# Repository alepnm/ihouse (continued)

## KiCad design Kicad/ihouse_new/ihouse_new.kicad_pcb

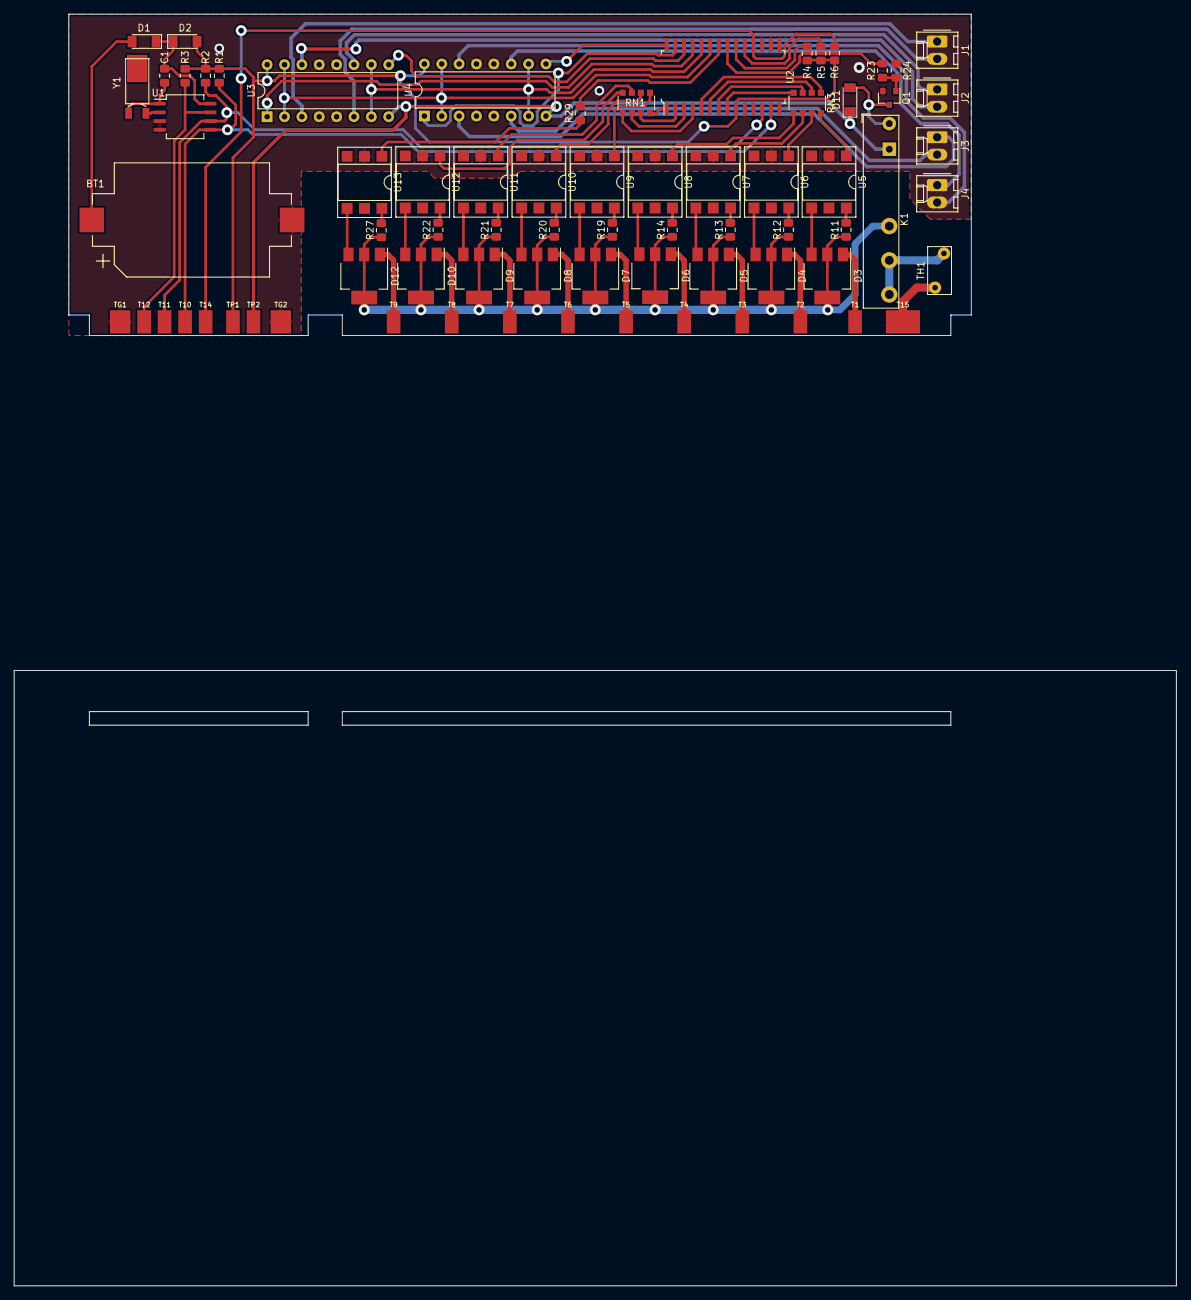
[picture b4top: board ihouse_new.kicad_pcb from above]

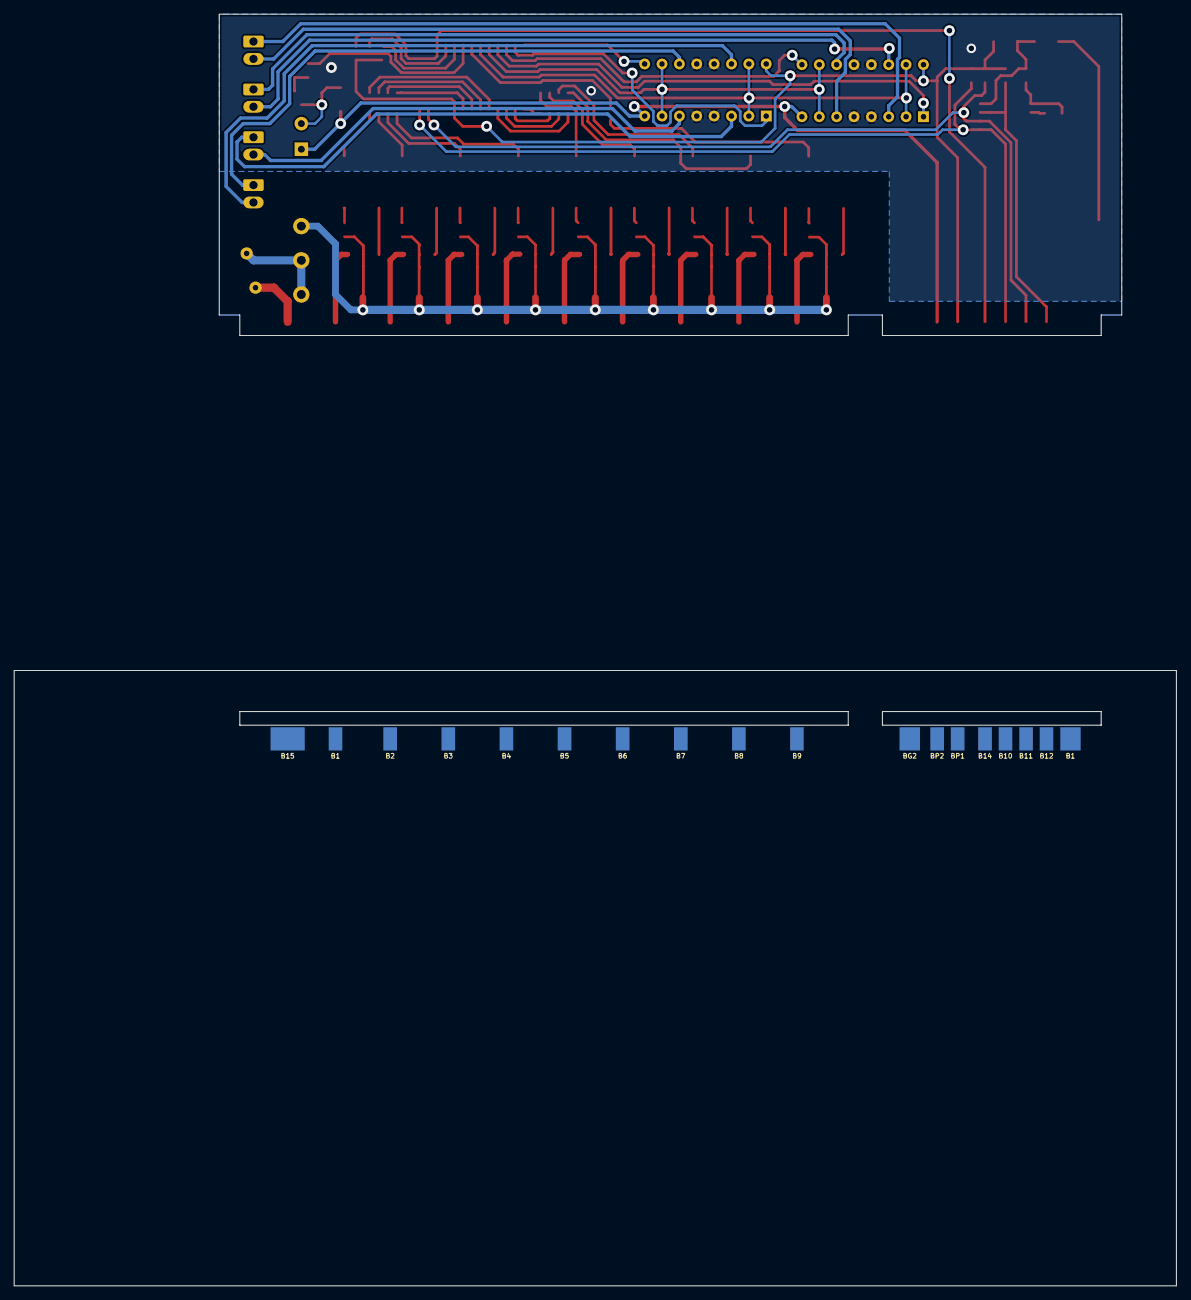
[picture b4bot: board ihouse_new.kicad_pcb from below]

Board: 2 copper layers, 132.0 x 47.0 mm, 91 parts (18 on the bottom side), 78 nets.

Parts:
B1, B1#2, B2, B3, B4, B5, B6, B7, B8, B9, B10, B11, B12, B14, B15: Conn_01x01; Sold_Pad
BG2: Conn_01x01; Sold_Pad
BP1, BP2: Conn_01x01; Sold_Pad
BT1: CR2032; BatteryHolder_Keystone_1060_1x2032
C1: 22p; C_0805_2012Metric_Pad1.15x1.40mm_HandSolder
D1: BAS85; D_MiniMELF
D2, D11: BAS32; D_MiniMELF
D3, D4, D5, D6, D7, D8, D9, D10, D12: Z0103MN; SOT-223
J1, J2, J3, J4: Valve 1; Molex_KK-254_AE-6410-02A_1x02_P2.54mm_Vertical
K1: FINDER-32.21-x000; Relay_SPDT_Finder_34.51_Vertical
Q1: BC817; SOT-23
R1, R2, R3, R4, R5, R6: 4.7k; R_0805_2012Metric_Pad1.15x1.40mm_HandSolder
R11, R12, R13, R14, R19, R20, R21, R22, R27, R29: 470; R_0805_2012Metric_Pad1.15x1.40mm_HandSolder
R23: 10k; R_0805_2012Metric_Pad1.15x1.40mm_HandSolder
R24: 1k; R_0805_2012Metric_Pad1.15x1.40mm_HandSolder
RN1, RN3: R_Pack04; R_Array_Convex_4x1206
T1, T2, T3, T4, T5, T6, T7, T8, T9, T10, T11, T12, T14, T15: Conn_01x01; Sold_Pad
TG1, TG2: Conn_01x01; Sold_Pad
TH1: Thermistor_PTC; RV_Disc_D7mm_W3.5mm_P5mm
TP1, TP2: Conn_01x01; Sold_Pad
U1: PCF8583T; SO-8_5.3x6.2mm_P1.27mm
U2: MCP23017-E_SO; SOIC-28_W7.5mm
U3, U4: L293D; DIP-16_W7.62mm
U5, U6, U7, U8, U9, U10, U11, U12, U13: MOC3063M; DIP-6_W7.62mm_SMDSocket_SmallPads
Y1: 32768; Crystal_SMD_FrontierElectronics_FM206

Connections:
+5V: BP1.1, D2.2, R1.1, R2.1, R3.1, R4.1, R5.1, R6.1, TP1.1, U2.9, U3.16, U4.16
+15V: BP2.1, D11.1, K1.A1, TP2.1, U3.8, U4.8
/ACL: D3.2, D3.4, D4.2, D4.4, D5.2, D5.4, D6.2, D6.4, D7.2, D7.4, D8.2, D8.4, D9.2, D9.4, D10.2, D10.4, D12.2, D12.4, K1.12, R11.1, R12.1, R13.1, R14.1, R19.1, R20.1, R21.1, R22.1, R27.1
/ACON: R23.2, U2.21
/M1ENA: U2.25, U3.1
/M2ENA: U2.26, U3.9
/M3ENA: U2.27, U4.1
/M4ENA: U2.28, U4.9
/MA: U2.23, U3.2, U3.15, U4.2, U4.15
/MB: U2.24, U3.7, U3.10, U4.7, U4.10
/OC1: RN3.8, U5.1
/OC2: RN3.7, U6.1
/OC3: RN3.6, U7.1
/OC4: RN3.5, U8.1
/OC5: RN1.5, U9.1
/OC6: RN1.6, U10.1
/OC7: RN1.7, U11.1
/OC8: RN1.8, U12.1
/OC9: R29.1, U13.1
/SCL: B11.1, R2.2, T11.1, U1.6, U2.12
/SDA: B10.1, R1.2, T10.1, U1.5, U2.13
/~INT: B12.1, R3.2, T12.1, U1.7
/~INTA: R4.2, U2.20
/~INTB: R5.2, U2.19
/~RST: B14.1, R6.2, T14.1, U2.18
GND: B1.1, BG2.1, BT1.2, Q1.2, R24.1, TG1.1, TG2.1, U1.3, U1.4, U2.10, U2.15, U2.16, U2.17, U3.4, U3.5, U3.12, U3.13, U4.4, U4.5, U4.12, U4.13, U5.2, U6.2, U7.2, U8.2, U9.2, U10.2, U11.2, U12.2, U13.2
unnamed: BT1.1, D1.2
unnamed: C1.1, D1.1, D2.1, U1.8
unnamed: C1.2, U1.1, Y1.2
unnamed: B1#2.1, D3.1, T1.1
unnamed: D3.3, U5.4
unnamed: B2.1, D4.1, T2.1
unnamed: D4.3, U6.4
unnamed: B3.1, D5.1, T3.1
unnamed: D5.3, U7.4
unnamed: B4.1, D6.1, T4.1
unnamed: D6.3, U8.4
unnamed: B5.1, D7.1, T5.1
unnamed: D7.3, U9.4
unnamed: B6.1, D8.1, T6.1
unnamed: D8.3, U10.4
unnamed: B7.1, D9.1, T7.1
unnamed: D9.3, U11.4
unnamed: B8.1, D10.1, T8.1
unnamed: D10.3, U12.4
unnamed: D11.2, K1.A2, Q1.3
unnamed: B9.1, D12.1, T9.1
unnamed: D12.3, U13.4
unnamed: J1.1, U3.3
unnamed: J1.2, U3.6
unnamed: J2.1, U3.11
unnamed: J2.2, U3.14
unnamed: J3.1, U4.3
unnamed: J3.2, U4.6
unnamed: J4.1, U4.11
unnamed: J4.2, U4.14
unnamed: K1.11, K1.14, TH1.1
unnamed: Q1.1, R23.1, R24.2
unnamed: R11.2, U5.6
unnamed: R12.2, U6.6
unnamed: R13.2, U7.6
unnamed: R14.2, U8.6
unnamed: R19.2, U9.6
unnamed: R20.2, U10.6
unnamed: R21.2, U11.6
unnamed: R22.2, U12.6
unnamed: R27.2, U13.6
unnamed: R29.2, U2.22
unnamed: RN1.1, U2.4
unnamed: RN1.2, U2.3
unnamed: RN1.3, U2.2
unnamed: RN1.4, U2.1
unnamed: RN3.1, U2.5
unnamed: RN3.2, U2.6
unnamed: RN3.3, U2.7
unnamed: RN3.4, U2.8
unnamed: B15.1, T15.1, TH1.2
unnamed: U1.2, Y1.1

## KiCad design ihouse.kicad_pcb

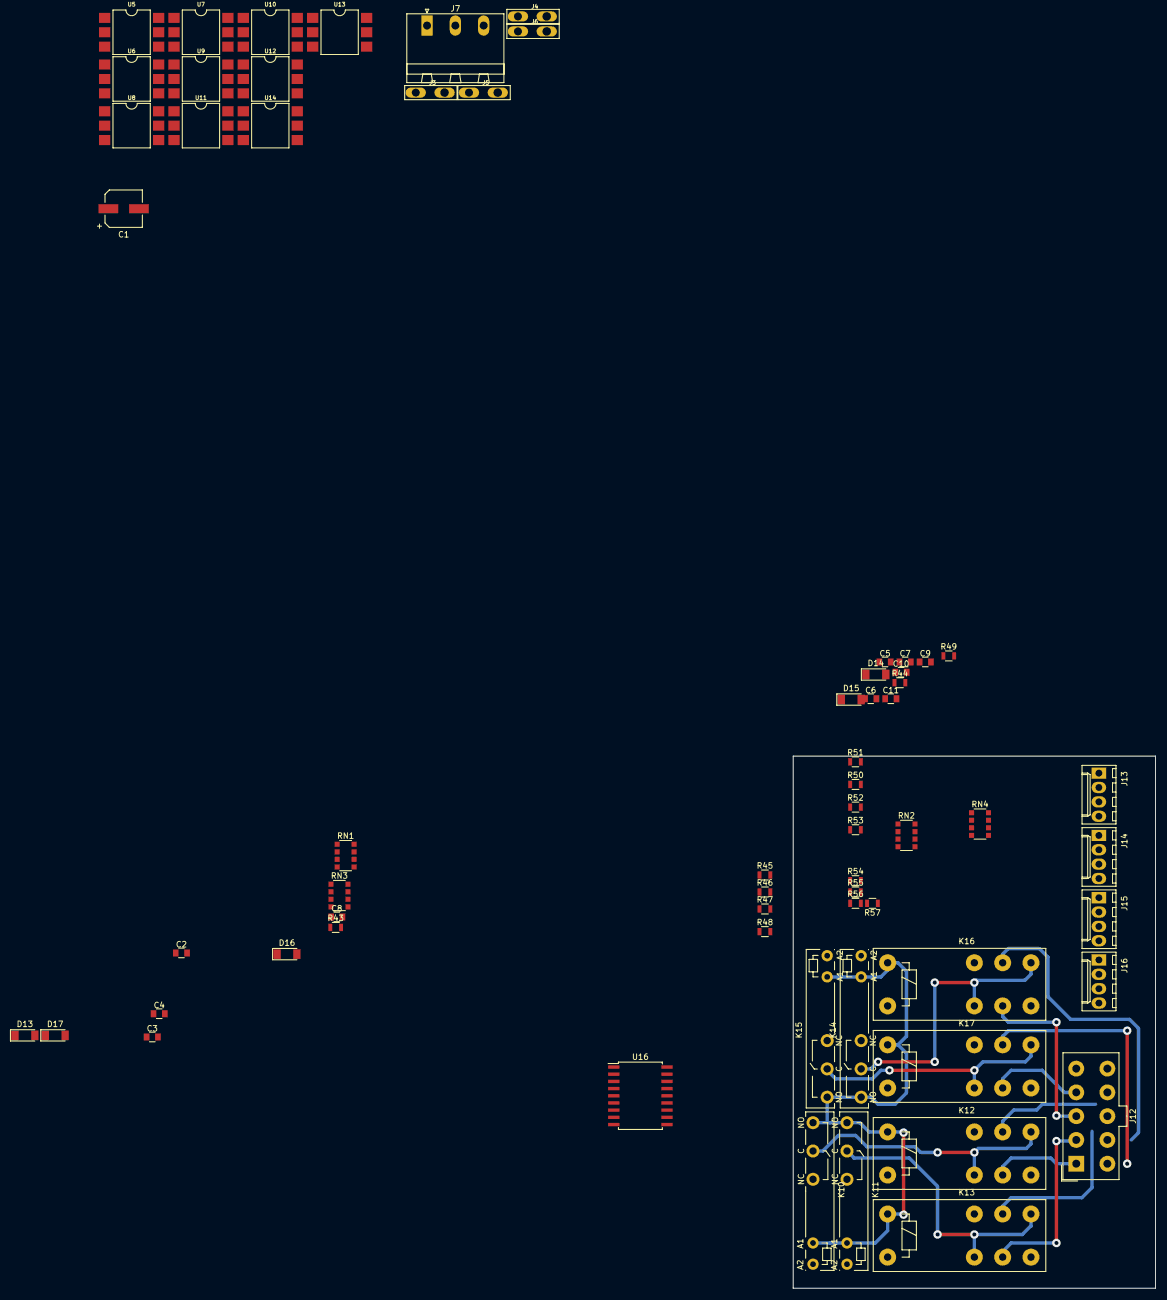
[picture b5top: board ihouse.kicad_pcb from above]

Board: 2 copper layers, 64.0 x 94.0 mm, 64 parts (0 on the bottom side), 38 nets.

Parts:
C1: 100uFx16V; CP_Elec_6.3x5.7
C2, C3, C4, C5, C6, C7, C8, C9, C10, C11: 0.1; C_0805
D13, D14, D15, D16, D17: D; D_MiniMELF
J3, J4, J5, J6: Conn_01x01; Faston_6.3x0.8x14
J7: Conn_01x03; PhoenixContact_MSTBA-G_03x5.00mm_Angled
J12: Valves; Molex_MiniFit-JR-5556-10A_2x05x4.20mm_Straight
J13, J14, J15, J16: Conn_01x04; Molex_KK-6410-04_04x2.54mm_Straight
K10, K11, K14, K15: FINDER-34.51; Relay_SPDT_SingleRow_Standing_FinderType34Point51
K12, K13, K16, K17: RT42xxxx; Relay_DPDT_Schrack-RT2-FormC_RM5mm
R43, R44, R45, R46, R47, R48, R49, R50, R51, R52, R53, R54, R55, R56, R57: R; R_0805
RN1, RN2, RN3, RN4: R_Pack04; R_Array_Convex_4x1206
U5, U6, U7, U8, U9, U10, U11, U12, U13, U14: MOC3060S; DIP-6_W9.53mm_SMD
U16: ULN2803A; SOIC-18W_7.5x11.6mm_Pitch1.27mm

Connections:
/DC sklendziu valdymas/3VDC: C2.1, D13.1, D14.1, D15.1, D16.1, D17.1, R43.2, R44.2, R49.1, RN3.5, RN3.6, RN3.7, RN3.8, RN4.5, RN4.6, RN4.7, RN4.8
/DC sklendziu valdymas/12VDC: K10.14, K10.A1, K11.14, K11.A1, K12.A1, K13.A1, K14.14, K14.A1, K15.14, K15.A1, K16.A1, K17.A1, R54.2, R55.2, R56.2, R57.2, U16.10
/DC sklendziu valdymas/COM: C2.2, C3.2, C4.1, C5.1, C6.1, C7.1, C8.1, C9.1, C10.1, C11.1, J13.2, J13.4, J14.2, J14.4, J15.2, J15.4, J16.2, J16.4, K12.12, K12.24, K13.12, K13.24, K16.12, K16.24, K17.12, K17.24, R45.1, R46.1, R47.1, R48.1, U16.9
/DC sklendziu valdymas/EXTI0: C4.2, J13.1, RN1.8, RN3.1
/DC sklendziu valdymas/EXTI1: C5.2, J13.3, RN1.7, RN3.2
/DC sklendziu valdymas/EXTI2: C6.2, J14.1, RN1.6, RN3.3
/DC sklendziu valdymas/EXTI3: C7.2, J14.3, RN1.5, RN3.4
/DC sklendziu valdymas/EXTI4: C8.2, J15.1, RN2.8, RN4.1
/DC sklendziu valdymas/EXTI5: C9.2, J15.3, RN2.7, RN4.2
/DC sklendziu valdymas/EXTI6: C10.2, J16.1, RN2.6, RN4.3
/DC sklendziu valdymas/EXTI7: C11.2, J16.3, RN2.5, RN4.4
/DC sklendziu valdymas/V1A1: J12.1, K12.21
/DC sklendziu valdymas/V1A2: J12.10, K12.11
/DC sklendziu valdymas/V1TP: D17.2, R48.2, R50.1
/DC sklendziu valdymas/V1TST: K10.11, K12.14, K12.22, R50.2, R54.1
/DC sklendziu valdymas/V2A1: J12.2, K13.21
/DC sklendziu valdymas/V2A2: J12.9, K13.11
/DC sklendziu valdymas/V2TP: D16.2, R47.2, R51.1
/DC sklendziu valdymas/V2TST: K11.11, K13.14, K13.22, R51.2, R55.1
/DC sklendziu valdymas/V3A1: J12.3, K16.21
/DC sklendziu valdymas/V3A2: J12.8, K16.11
/DC sklendziu valdymas/V3TP: D14.2, R46.2, R52.1
/DC sklendziu valdymas/V3TST: K14.11, K16.14, K16.22, R52.2, R56.1
/DC sklendziu valdymas/V4A1: J12.4, K17.21
/DC sklendziu valdymas/V4A2: J12.7, K17.11
/DC sklendziu valdymas/V4TP: D13.2, R45.2, R53.1
/DC sklendziu valdymas/V4TST: K15.11, K17.14, K17.22, R53.2, R57.1
/DC sklendziu valdymas/~MCPRST: C3.1, D15.2, R49.2
/PE: J3.1, J4.1, J5.1, J6.1, J7.3
/Power outputs/OUTAC9: U5.4, U14.4
unnamed: K10.A2, U16.18
unnamed: K11.A2, U16.16
unnamed: K12.A2, U16.17
unnamed: K13.A2, U16.15
unnamed: K14.A2, U16.14
unnamed: K15.A2, U16.12
unnamed: K16.A2, U16.13
unnamed: K17.A2, U16.11

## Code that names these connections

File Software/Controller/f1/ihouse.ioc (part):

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Mcu.Name=STM32F103C(8-B)Tx
Mcu.Package=LQFP48
Mcu.UserName=STM32F103C8Tx
PA0-WKUP.GPIOParameters=GPIO_PuPd,GPIO_Label
PA0-WKUP.GPIO_Label=VLINE
PA0-WKUP.GPIO_PuPd=GPIO_PULLUP
PA0-WKUP.Signal=GPIO_Input
PA1.GPIOParameters=GPIO_Label
PA1.GPIO_Label=LEAK1
PA1.Signal=ADCx_IN1
PA10.GPIOParameters=GPIO_Label
PA10.GPIO_Label=TBTX
PA10.Mode=Asynchronous
PA10.Signal=USART1_RX
PA11.GPIOParameters=GPIO_Label
PA11.GPIO_Label=BUZZ
PA11.Signal=S_TIM1_CH4
PA13.Mode=Serial_Wire
PA13.Signal=SYS_JTMS-SWDIO
PA14.Mode=Serial_Wire
PA14.Signal=SYS_JTCK-SWCLK
PA2.Mode=Asynchronous
PA2.Signal=USART2_TX
PA3.Mode=Asynchronous
PA3.Signal=USART2_RX
PA4.GPIOParameters=GPIO_Label
PA4.GPIO_Label=LEAK2
PA4.Signal=ADCx_IN4
PA5.GPIOParameters=GPIO_Label
PA5.GPIO_Label=LEAK3
PA5.Signal=ADCx_IN5
PA6.GPIOParameters=GPIO_PuPd,GPIO_Label
PA6.GPIO_Label=OPTIC
PA6.GPIO_PuPd=GPIO_PULLUP
PA6.Signal=GPIO_Input
PA7.GPIOParameters=GPIO_PuPd,GPIO_Label
PA7.GPIO_Label=OPTIC_WC
PA7.GPIO_PuPd=GPIO_PULLUP
PA7.Signal=GPIO_Input
PA8.GPIOParameters=GPIO_PuPd,GPIO_Label
PA8.GPIO_Label=RCEN
PA8.GPIO_PuPd=GPIO_PULLUP
PA8.Signal=GPIO_Input
PA9.GPIOParameters=GPIO_Label
PA9.GPIO_Label=TBRX
PA9.Mode=Asynchronous
PA9.Signal=USART1_TX
PB0.GPIOParameters=GPIO_Label
PB0.GPIO_Label=PWM3
PB0.Signal=S_TIM3_CH3
PB1.GPIOParameters=GPIO_Label
PB1.GPIO_Label=PWM4
PB1.Signal=S_TIM3_CH4
PB10.GPIOParameters=GPIO_PuPd,GPIO_Label
PB10.GPIO_Label=QCH_D2
PB10.GPIO_PuPd=GPIO_PULLUP
PB10.Signal=GPIO_Input
PB11.GPIOParameters=GPIO_PuPd,GPIO_Label
PB11.GPIO_Label=QCH_D3
PB11.GPIO_PuPd=GPIO_PULLUP
PB11.Signal=GPIO_Input
PB12.GPIOParameters=PinState,GPIO_PuPd,GPIO_Label,GPIO_ModeDefaultOutputPP
PB12.GPIO_Label=MCPRST
PB12.GPIO_ModeDefaultOutputPP=GPIO_MODE_OUTPUT_PP
PB12.GPIO_PuPd=GPIO_NOPULL
PB12.PinState=GPIO_PIN_SET
PB12.Signal=GPIO_Output
PB13.GPIOParameters=PinState,GPIO_PuPd,GPIO_Label
PB13.GPIO_Label=M1ENA
PB13.GPIO_PuPd=GPIO_NOPULL
PB13.PinState=GPIO_PIN_SET
PB13.Signal=GPIO_Output
PB14.GPIOParameters=PinState,GPIO_Label
PB14.GPIO_Label=M23ENA
PB14.PinState=GPIO_PIN_SET
PB14.Signal=GPIO_Output
PB15.GPIOParameters=PinState,GPIO_Label,GPIO_ModeDefaultOutputPP
PB15.GPIO_Label=TBCMD
PB15.GPIO_ModeDefaultOutputPP=GPIO_MODE_OUTPUT_PP
PB15.PinState=GPIO_PIN_SET
PB15.Signal=GPIO_Output
PB2.GPIOParameters=GPIO_PuPd,GPIO_Label
PB2.GPIO_Label=USER_SW
PB2.GPIO_PuPd=GPIO_PULLUP
PB2.Signal=GPIO_Input
PB3.GPIOParameters=GPIO_PuPd,GPIO_Label
PB3.GPIO_Label=LPULSE
PB3.GPIO_PuPd=GPIO_PULLUP
PB3.Signal=GPIO_Input
PB4.GPIOParameters=GPIO_Label
PB4.GPIO_Label=PWM1
PB4.Signal=S_TIM3_CH1
PB5.GPIOParameters=GPIO_Label
PB5.GPIO_Label=PWM2
PB5.Signal=S_TIM3_CH2
PB6.Mode=I2C
PB6.Signal=I2C1_SCL
PB7.Mode=I2C
PB7.Signal=I2C1_SDA
PB8.GPIOParameters=GPIO_PuPd,GPIO_Label
PB8.GPIO_Label=QCH_D0
PB8.GPIO_PuPd=GPIO_PULLUP
PB8.Signal=GPIO_Input
PB9.GPIOParameters=GPIO_PuPd,GPIO_Label
PB9.GPIO_Label=QCH_D1
PB9.GPIO_PuPd=GPIO_PULLUP
PB9.Signal=GPIO_Input
PC13-TAMPER-RTC.GPIOParameters=GPIO_Speed,PinState,GPIO_PuPd,GPIO_Label
PC13-TAMPER-RTC.GPIO_Label=DHTIO
PC13-TAMPER-RTC.GPIO_PuPd=GPIO_NOPULL
PC13-TAMPER-RTC.GPIO_Speed=GPIO_SPEED_FREQ_HIGH
PC13-TAMPER-RTC.PinState=GPIO_PIN_SET
PC13-TAMPER-RTC.Signal=GPIO_Output
PC14-OSC32_IN.Mode=LSE-External-Oscillator
PC14-OSC32_IN.Signal=RCC_OSC32_IN
PC15-OSC32_OUT.Mode=LSE-External-Oscillator
PC15-OSC32_OUT.Signal=RCC_OSC32_OUT
PD0-OSC_IN.Mode=HSE-External-Oscillator
PD0-OSC_IN.Signal=RCC_OSC_IN
PD1-OSC_OUT.Mode=HSE-External-Oscillator
PD1-OSC_OUT.Signal=RCC_OSC_OUT
RCC.SYSCLKFreq_VALUE=48000000
RCC.SYSCLKSource=RCC_SYSCLKSOURCE_PLLCLK
board=custom

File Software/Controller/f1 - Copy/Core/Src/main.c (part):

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            /* button B - virtuves darbines zonos apsvietimas pilnas/dalinis */
            if( LL_GPIO_IsInputPinSet(GPIOB, LL_GPIO_PIN_8) ) {

                //MCP23017_TogglePin(&REL10);

                //while( LL_GPIO_IsInputPinSet(GPIOB, LL_GPIO_PIN_8) );
            }
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            /* button C -  */
            if( LL_GPIO_IsInputPinSet(GPIOA, LL_GPIO_PIN_12) ) {

                //MCP23017_TogglePin(&REL11);

                //while( LL_GPIO_IsInputPinSet(GPIOA, LL_GPIO_PIN_12) );
            }
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            /* button D -  */
            if( LL_GPIO_IsInputPinSet(GPIOA, LL_GPIO_PIN_11) ) {

                //MCP23017_TogglePin(&REL12);

                //while( LL_GPIO_IsInputPinSet(GPIOA, LL_GPIO_PIN_11) );
            }
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
  LL_APB2_GRP1_EnableClock(LL_APB2_GRP1_PERIPH_GPIOA);
  /**ADC1 GPIO Configuration
  PA0-WKUP   ------> ADC1_IN0
  PA1   ------> ADC1_IN1
  PA4   ------> ADC1_IN4
  PA5   ------> ADC1_IN5
  PA6   ------> ADC1_IN6
  PA7   ------> ADC1_IN7
  */
  GPIO_InitStruct.Pin = OPTIC_Pin|HUM1_Pin|HUM2_Pin|HUM3_Pin
                          |TEMP_Pin|VLINE_Pin;
  GPIO_InitStruct.Mode = LL_GPIO_MODE_ANALOG;
  LL_GPIO_Init(GPIOA, &GPIO_InitStruct);

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  PA9   ------> USART1_TX
  PA10   ------> USART1_RX
  */
  GPIO_InitStruct.Pin = TBRX_Pin;
  GPIO_InitStruct.Mode = LL_GPIO_MODE_ALTERNATE;
  GPIO_InitStruct.Speed = LL_GPIO_SPEED_FREQ_HIGH;
  GPIO_InitStruct.OutputType = LL_GPIO_OUTPUT_PUSHPULL;
  LL_GPIO_Init(TBRX_GPIO_Port, &GPIO_InitStruct);

  GPIO_InitStruct.Pin = TBTX_Pin;
  GPIO_InitStruct.Mode = LL_GPIO_MODE_FLOATING;
  LL_GPIO_Init(TBTX_GPIO_Port, &GPIO_InitStruct);

  /* USART1 interrupt Init */
  NVIC_SetPriority(USART1_IRQn, NVIC_EncodePriority(NVIC_GetPriorityGrouping(),0, 0));
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
  LL_APB2_GRP1_EnableClock(LL_APB2_GRP1_PERIPH_GPIOA);
  /**USART2 GPIO Configuration
  PA2   ------> USART2_TX
  PA3   ------> USART2_RX
  */
  GPIO_InitStruct.Pin = LL_GPIO_PIN_2;
  GPIO_InitStruct.Mode = LL_GPIO_MODE_ALTERNATE;
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  LL_GPIO_ResetOutputPin(GPIOC, LL_GPIO_PIN_13);

  /**/
  LL_GPIO_ResetOutputPin(M23ENA_GPIO_Port, M23ENA_Pin);

  /**/
  LL_GPIO_SetOutputPin(GPIOB, MCPRST_Pin|M1ENA_Pin|TBCMD_Pin);

  /**/
  GPIO_InitStruct.Pin = LL_GPIO_PIN_13;
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  LL_GPIO_Init(GPIOC, &GPIO_InitStruct);

  /**/
  GPIO_InitStruct.Pin = DS18B20_IO_Pin|LPULSE1_Pin|LPULSE2_Pin|LPULSE_Pin
                          |QCH_D0_Pin|QCH_D1_Pin;
  GPIO_InitStruct.Mode = LL_GPIO_MODE_FLOATING;
  LL_GPIO_Init(GPIOB, &GPIO_InitStruct);

  /**/
  GPIO_InitStruct.Pin = MCPRST_Pin|M1ENA_Pin|M23ENA_Pin|TBCMD_Pin;
  GPIO_InitStruct.Mode = LL_GPIO_MODE_OUTPUT;
  GPIO_InitStruct.Speed = LL_GPIO_SPEED_FREQ_LOW;
  GPIO_InitStruct.OutputType = LL_GPIO_OUTPUT_PUSHPULL;
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
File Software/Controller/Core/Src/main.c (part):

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MCP_Output_TypeDef OC7 = {MCP_GPIOB, PIN_2};
MCP_Output_TypeDef OC8 = {MCP_GPIOB, PIN_3};
MCP_Output_TypeDef OC9 = {MCP_GPIOA, PIN_1};
MCP_Output_TypeDef ACON = {MCP_GPIOA, PIN_0};
MCP_Output_TypeDef MA = {MCP_GPIOA, PIN_2};
MCP_Output_TypeDef MB = {MCP_GPIOA, PIN_3};
MCP_Output_TypeDef M1ENA = {MCP_GPIOA, PIN_4};
MCP_Output_TypeDef M2ENA = {MCP_GPIOA, PIN_5};
MCP_Output_TypeDef M3ENA = {MCP_GPIOA, PIN_6};
MCP_Output_TypeDef M4ENA = {MCP_GPIOA, PIN_7};


/* USER CODE END PV */
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
  LL_AHB1_GRP1_EnableClock(LL_AHB1_GRP1_PERIPH_GPIOA);
  /**ADC GPIO Configuration
  PA0   ------> ADC_IN0
  PA4   ------> ADC_IN4
  */
  GPIO_InitStruct.Pin = VLINE_Pin;
  GPIO_InitStruct.Mode = LL_GPIO_MODE_ANALOG;
  GPIO_InitStruct.Pull = LL_GPIO_PULL_NO;
  LL_GPIO_Init(VLINE_GPIO_Port, &GPIO_InitStruct);

  GPIO_InitStruct.Pin = OPTIC_Pin;
  GPIO_InitStruct.Mode = LL_GPIO_MODE_ANALOG;
  GPIO_InitStruct.Pull = LL_GPIO_PULL_NO;
  LL_GPIO_Init(OPTIC_GPIO_Port, &GPIO_InitStruct);

  /* USER CODE BEGIN ADC_Init 1 */

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  /* USER CODE END TIM16_Init 2 */
  LL_AHB1_GRP1_EnableClock(LL_AHB1_GRP1_PERIPH_GPIOA);
  /**TIM16 GPIO Configuration
  PA6   ------> TIM16_CH1
  */
  GPIO_InitStruct.Pin = BUZZ_Pin;
  GPIO_InitStruct.Mode = LL_GPIO_MODE_ALTERNATE;
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
  LL_AHB1_GRP1_EnableClock(LL_AHB1_GRP1_PERIPH_GPIOA);
  /**USART2 GPIO Configuration
  PA1   ------> USART2_DE
  PA2   ------> USART2_TX
  PA3   ------> USART2_RX
  */
  GPIO_InitStruct.Pin = LL_GPIO_PIN_1;
  GPIO_InitStruct.Mode = LL_GPIO_MODE_ALTERNATE;
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  LL_SYSCFG_SetEXTISource(LL_SYSCFG_EXTI_PORTB, LL_SYSCFG_EXTI_LINE11);

  /**/
  LL_GPIO_SetPinPull(LPULSE_GPIO_Port, LPULSE_Pin, LL_GPIO_PULL_NO);

  /**/
  LL_GPIO_SetPinMode(LPULSE_GPIO_Port, LPULSE_Pin, LL_GPIO_MODE_INPUT);

  /**/
  EXTI_InitStruct.Line_0_31 = LL_EXTI_LINE_11;
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
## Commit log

2018-10-16 pradine inicializacija
2018-10-16 schemos paruosimas
2018-10-17 tarpinis komitas
2019-01-02 tarpinis kommitas
2019-01-04 sukurtas embitz proektas
2019-01-07 pertvarkyta projekto struktura. pridetas Nextion projektas
2019-01-07 schemos ir pcb failai perkelti i atskira folderi
2019-01-08 projekto issaugojimas pries bandyma implementuoti Freertos
2019-01-08 modbasas veikia
2019-01-22 pataisyta schema, sukonfiguruotas uartas per dma
2019-01-24 schemos, pcb paruosimas
2019-01-29 Software/Controller/Core/libs/pcf8574/pcf8574.c Software/Controller/Core/libs/pcf8574/pcf8574.h LCD1602 per I2C kodo rasymas
2019-01-29 Software/Controller/Core/libs/pcf8574/pcf8574_lcd.h
2019-02-27 datasheetai, ivairiu rtc taimeriu moduliai
2019-02-28 schema
2019-03-01 pcb plokstes projektavimas
2019-03-07 rtc pcf8523 modulio rasymas, pataisymai i2c modulyje
2019-03-07 mcp23017 modulio rasymas
2019-03-27 repo reinicializavimas
2019-03-27 principines schemos, pcb ruosimas
2019-03-28 schemos ir pcb paruosimas
2019-03-28 schemos ir pcb ruosimas
2019-04-04 schemos ir pcb paruosymas
2019-04-05 plokstes pataisymai
2019-04-07 programos rasymas, schemos ir pcb koregavimai. veikia stm bootloaderis per Demonstrator
2019-04-08 schemos, pcb ruosimas
2019-04-08 schemos ir pcb plokstes ruosimas
2019-04-11 sukurti nauji moduliai - usart, rtc, tb387
2019-04-14 tb387 modulio rasymas
2019-04-15 prideta schema ir pcb lcd ekrano rs232 draiverio
2019-04-16 2019.04.16
2019-04-16 2019-04-17
2019-04-18 2019-04-18
2019-04-18 2019-04-19
2019-04-22 20190423
2019-04-23 2019.04.23
2019-05-13 i2c modulio tvarkymas, ds1307 modulio tvarkymas. ds1307 veikia
2019-05-13 ds1307 modulis, drakon diagramos
2019-05-14 ds18b20 modulis
2019-05-15 bandymai su stp32 backup registrais
2019-05-15 2019-05-15
2019-05-16 2019.05.16
2019-05-17 20190517
2019-05-19 2019.05.19
2019-05-20 20190521
2019-05-23 pridetas testinis projektas
2019-05-23 20190524
2019-06-26 versija 1.0
2019-06-28 nupiesta paskirstymo dezutes schema ir pcb
2019-07-05 schemos korekcijos ir ploksciu paruosimas
